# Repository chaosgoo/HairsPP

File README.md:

# HairsPP

语言: 中文, [English](README.En.md)

[HairsPP](https://github.com/chaosgoo/HairsPP) 是Hairs Plus Plus的简写。[HairsPP](https://github.com/chaosgoo/HairsPP)是一个三键的机械键盘。
* 支持热插拔
* 支持连发模式
* 易学的源码
* 自定义按键映射

## TODO
* ~~20210412:电路~~ 
* ~~20210418:初版源码~~ 
* 壳体 
* PC端配置软件

## 食用指南
开关状态(左5号右6号) | 模式名称 | 描述 
:-:|:-:|:-:
00 | 配置模式 | 串口发送三个字符会自动分配到三个键上，一切正常串口会收到"ok"字符。
10 | 连发模式 | 按住按钮会不断触发点击事件
01 | 复位模式 | 恢复默认键位，通电前配置才有效
11 | 常规模式 | 普通键盘的普通行为

## 材料清单

序号 | 名称 | 数量 | 备注
-|-|-|-
1|ATMega32u4 | 1 | 主控芯片 QFN44封装
2|AP2112K-3.3 | 1 | 5V转3.3V芯片 SOT-23-5
3|16Mhz晶振 | 1 | 2.0*1.6
4|1uF电容 | 1 | 0603
5|22pf电容 | 2 | 0603
6|10uf电容 | 2 | 0603
7|1KΩ电阻 | 5 | 0805
8|10KΩ电阻 | 1 | 0805
9|22Ω电阻 | 2 | 0805
10|凯华热插拔轴座 | 3 | 1511系列
11|轴体 | 3 | 任意轴体
12|2位拨码开关 | 1 | 1.27mm
13|Type-C接口 | 1 | 16p
14|肖特基二极管 | 1 | BAT60JFILM SOD-323
15|微动开关 | 1 | 3x4x2.5 四脚贴片

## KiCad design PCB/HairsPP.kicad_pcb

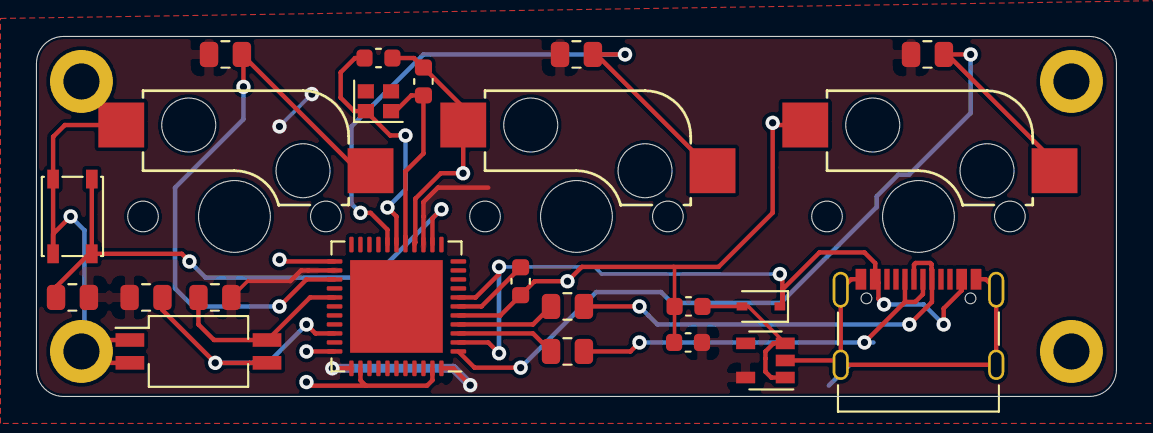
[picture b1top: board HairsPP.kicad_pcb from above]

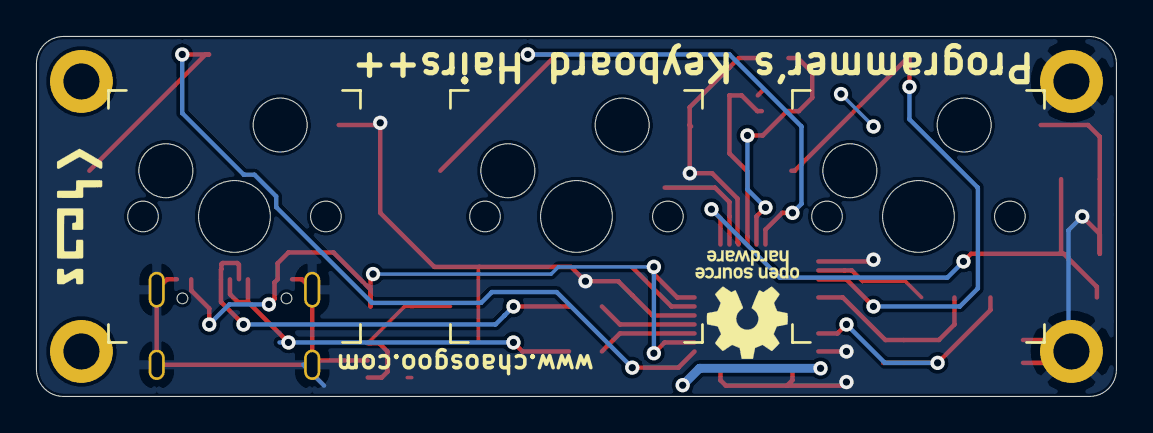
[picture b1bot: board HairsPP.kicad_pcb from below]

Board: 2 copper layers, 60.0 x 20.0 mm, 27 parts (3 on the bottom side), 17 nets.

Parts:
16MHz1: Crystal; Crystal_SMD_2016-4Pin_2.0x1.6mm
C1: 1uF; C_0603_1608Metric
C2, C4: 22pF; C_0603_1608Metric
C13: 10; C_0603_1608Metric
C19: 10uF; C_0603_1608Metric
D2: SD36_SOD323; D_SOD-323
J1: USB_C_Receptacle_USB2.0; USB_C_Receptacle_Palconn_UTC16-G
J2, J3, J4, J5: Conn_01x01; ScrewM2_SMT
MCU1: ATmega32U4-AU; QFN-44-1EP_7x7mm_P0.5mm_EP5.15x5.15mm
R1, R3, R4, R6, R8: 1K; R_0805_2012Metric
R2: 10K; R_0805_2012Metric
R5, R7: 22; R_0805_2012Metric
SW1, SW2, SW3: SW_Push; Kailh_socket_MX
SW4: SW_Push; SW_SPST_PTS810
SW5: SW_DIP_x02; SW_DIP_SPSTx02_Slide_Copal_CHS-02B_W7.62mm_P1.27mm
U1: AP2112K-3.3; SOT-23-5

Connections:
D4: MCU1.25, R1.2, SW1.2
D5: MCU1.31, R6.2, SW5.3
D6: MCU1.27, R8.2, SW5.4
D7: MCU1.1, R3.2, SW2.2
D+: MCU1.4, R7.1
D-: MCU1.3, R5.1
GND: C1.2, C2.2, C4.2, C13.2, C19.2, J1.A1, J1.A12, J1.B1, J1.B12, J1.S1, J4.1, J5.1, MCU1.5, MCU1.15, MCU1.23, MCU1.33, MCU1.35, MCU1.43, SW1.1, SW2.1, SW3.1, SW4.1, SW5.1, SW5.2, U1.2
unnamed: 16MHz1.1, C2.1, MCU1.17
unnamed: 16MHz1.2, C4.1, MCU1.16
unnamed: C19.1, D2.2, U1.1, U1.3
unnamed: J1.A6, J1.B6, R7.2
unnamed: J1.A7, J1.B7, R5.2
unnamed: MCU1.13, R2.2, SW4.2
SCL|D3: MCU1.18, R4.2, SW3.2
UCAP: C1.1, MCU1.6
VCC: C13.1, MCU1.14, MCU1.24, MCU1.34, MCU1.44, R1.1, R2.1, R3.1, R4.1, R6.1, R8.1, U1.5
V_USB: D2.1, J1.A4, J1.A9, J1.B4, J1.B9, MCU1.2, MCU1.7

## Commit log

2021-04-18 Add introduction
2021-04-18 添加按键映射功能
2021-04-26 1.更新材料清单
2021-05-04 增加串口修改键位功能

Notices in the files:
README.md:
https://img.shields.io/badge/license-GNU-blue.svg?style=flat-square
